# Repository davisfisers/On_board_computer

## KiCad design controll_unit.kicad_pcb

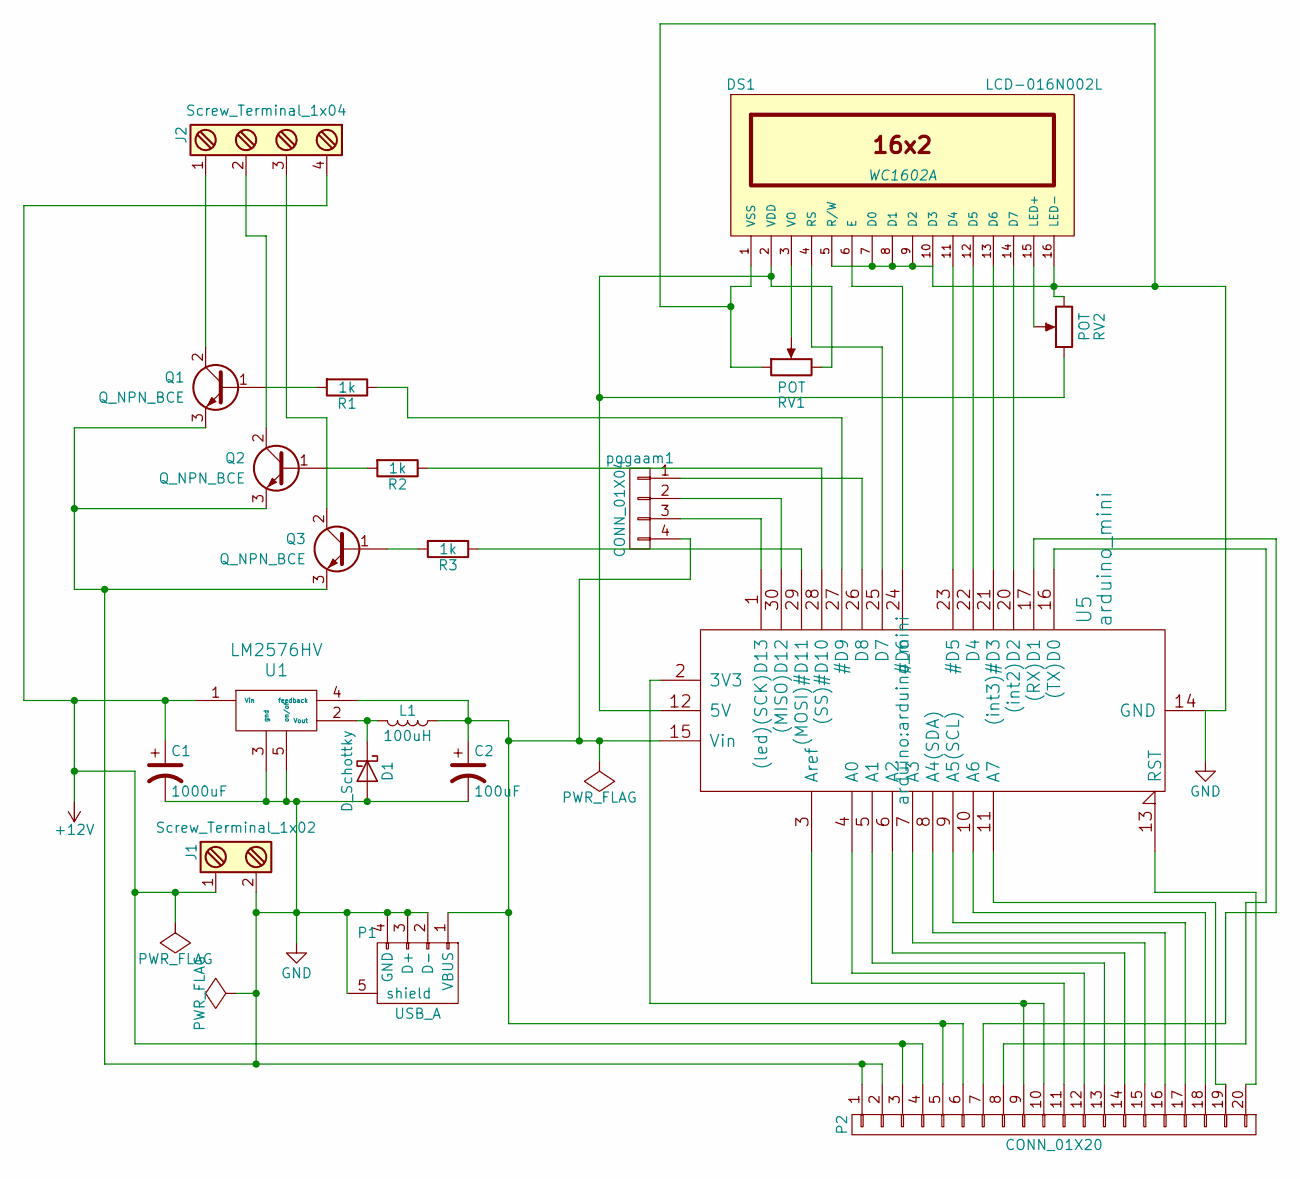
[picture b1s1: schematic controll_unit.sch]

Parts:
C1: 1000uF; CP_Radial_D12.5mm_P5.00mm
C2: 100uF; CP_Radial_D5.0mm_P2.00mm
D1: D_Schottky; D_DO-41_SOD81_P10.16mm_Horizontal
DS1: LCD-016N002L; WC1602A
J1: Screw_Terminal_1x02; TerminalBlock_Pheonix_PT-3.5mm_2pol
J2: Screw_Terminal_1x04; TerminalBlock_Pheonix_PT-3.5mm_4pol
L1: 100uH; Neosid_Inductor_Sd75
P1: USB_A
P2: CONN_01X20; IDC_Header_Straight_20pins
Q1, Q2, Q3: Q_NPN_BCE; TO-220_Vertical
R1, R2, R3: 1k; R_Axial_DIN0617_L17.0mm_D6.0mm_P25.40mm_Horizontal
RV1, RV2: POT; Potentiometer_Trimmer_Piher_PT-10v5_Horizontal_Px5.0mm_Py5.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
U1: LM2576HV; TO-220-5_Pentawatt_Multiwatt-5_Vertical
U5: arduino_mini
pogaam1: CONN_01X04; bornier4

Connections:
+12V: C1.1, J1.1, J2.4, P2.3, P2.4, U1.1 (Vin)
GND: C1.2, C2.2, D1.2 (A), DS1.1 (VSS), DS1.5 (R/W), DS1.7 (D0), DS1.8 (D1), DS1.9 (D2), DS1.10 (D3), DS1.16 (LED-), J1.2, P1.2 (D-), P1.3 (D+), P1.4 (GND), P1.5 (shield), P2.1, P2.2, Q1.3 (E), Q2.3 (E), Q3.3 (E), RV1.1, RV2.3, U1.3 (gnd), U1.5 (on/of), U5.14 (GND), U5.19 (GND)
unnamed: C2.1, L1.1, P1.1 (VBUS), P2.5, P2.6, U1.4 (feedback), U5.15 (Vin), pogaam1.4
unnamed: D1.1 (K), L1.2, U1.2 (Vout)
unnamed: DS1.2 (VDD), RV1.3, RV2.1, U5.12 (5V)
unnamed: DS1.3 (VO), RV1.2
unnamed: DS1.4 (RS), U5.25 (D7)
unnamed: DS1.6 (E), U5.24 (#D6)
unnamed: DS1.11 (D4), U5.23 (#D5)
unnamed: DS1.12 (D5), U5.22 (D4)
unnamed: DS1.13 (D6), U5.21 ((int3)#D3)
unnamed: DS1.14 (D7), U5.20 ((int2)D2)
unnamed: DS1.15 (LED+), RV2.2
unnamed: J2.1, Q1.2 (C)
unnamed: J2.2, Q2.2 (C)
unnamed: J2.3, Q3.2 (C)
unnamed: P2.7, U5.17 ((RX)D1)
unnamed: P2.8, U5.16 ((TX)D0)
unnamed: P2.9, P2.10, U5.2 (3V3)
unnamed: P2.11, U5.3 (Aref)
unnamed: P2.12, U5.4 (A0)
unnamed: P2.13, U5.5 (A1)
unnamed: P2.14, U5.6 (A2)
unnamed: P2.15, U5.7 (A3)
unnamed: P2.16, U5.8 (A4(SDA))
unnamed: P2.17, U5.9 (A5(SCL))
unnamed: P2.18, U5.10 (A6)
unnamed: P2.19, U5.11 (A7)
unnamed: P2.20, U5.13 (RST)
unnamed: Q1.1 (B), R1.2
unnamed: Q2.1 (B), R2.2
unnamed: Q3.1 (B), R3.2
unnamed: R1.1, U5.27 (#D9)
unnamed: R2.1, U5.28 ((SS)#D10)
unnamed: R3.1, U5.29 ((MOSI)#D11)
unnamed: U5.1 ((led)(SCK)D13), pogaam1.3
unnamed: U5.26 (D8), pogaam1.1
unnamed: U5.30 ((MISO)D12), pogaam1.2

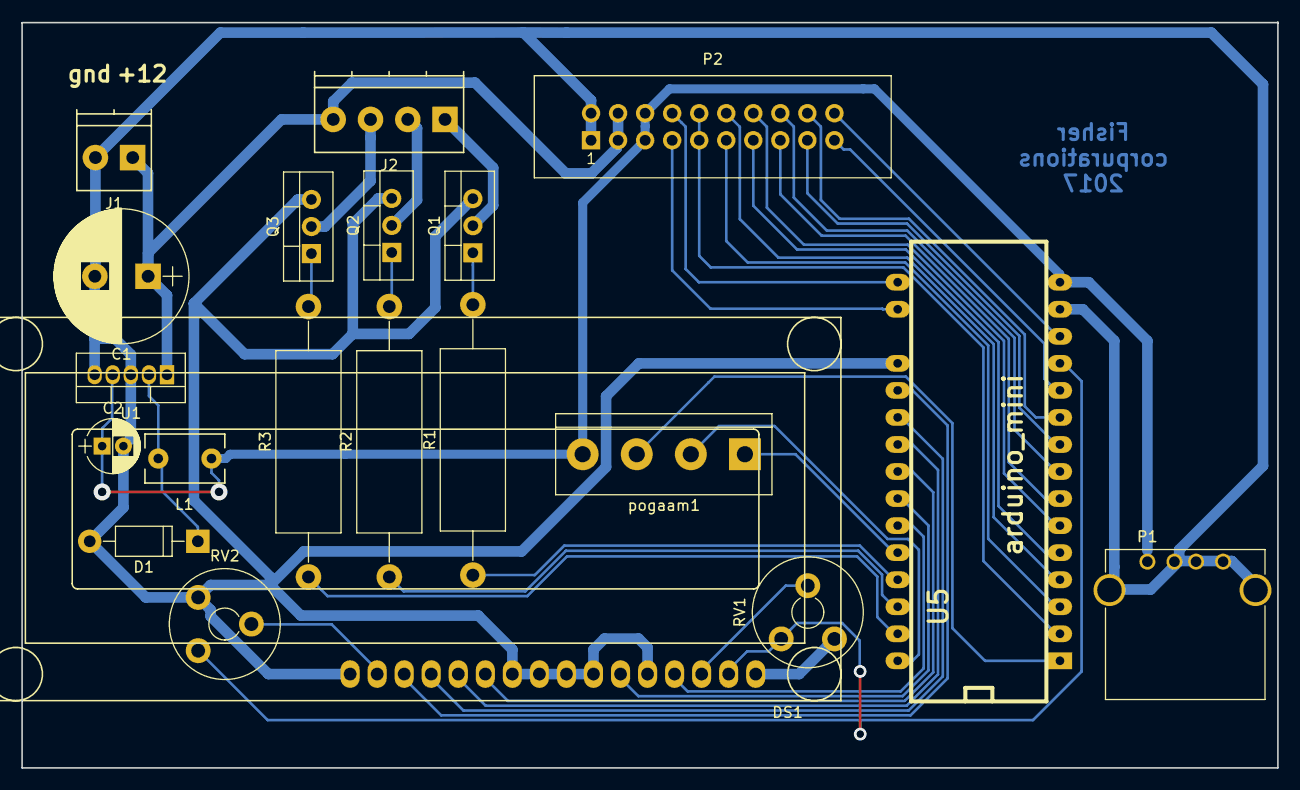
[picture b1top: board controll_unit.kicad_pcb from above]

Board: 2 copper layers, 118.0 x 70.1 mm, 20 parts (0 on the bottom side), 38 nets.

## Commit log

2019-03-23 upload
